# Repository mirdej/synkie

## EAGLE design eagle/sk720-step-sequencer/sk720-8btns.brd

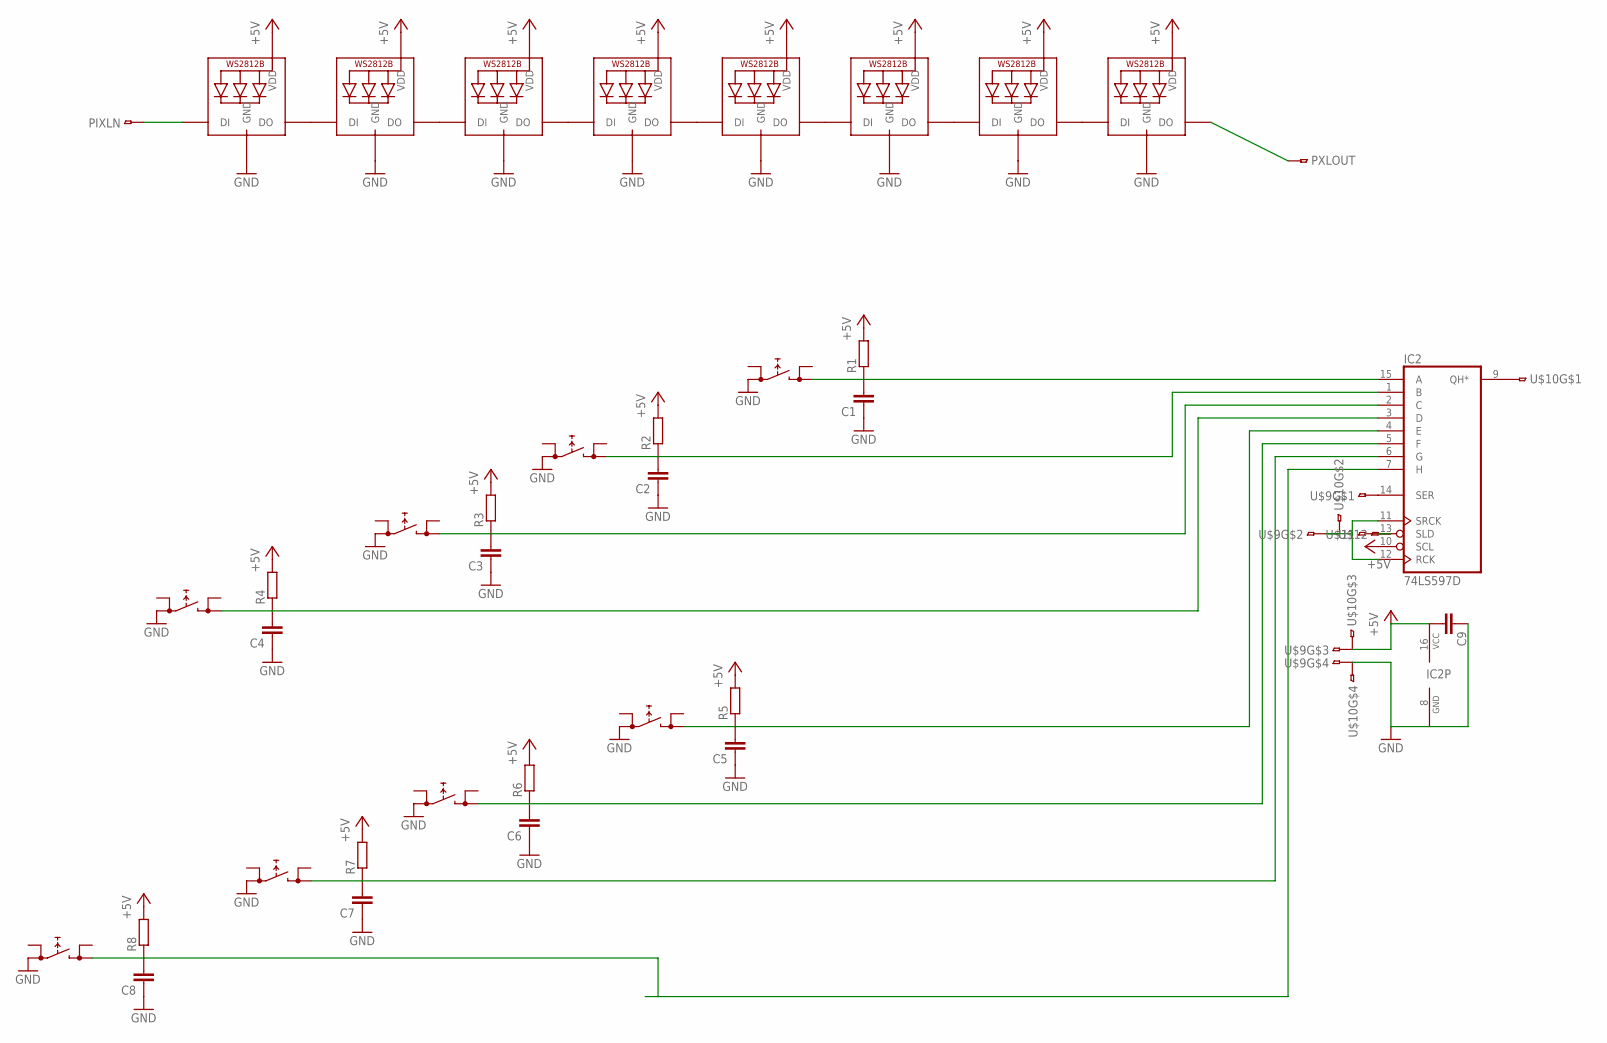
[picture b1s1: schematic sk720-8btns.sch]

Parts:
C1, C2, C3, C4, C5, C6, C7, C8: C-EUC0603; C0603
C9: C-EUC1206; C1206
IC2: 74LS597D; SO16
LED1, LED2, LED3, LED4, LED5, LED6, LED7, LED8: WS2812B5050; WS2812B
PIXLN: 1PINSMD
PXLOUT: 1PINSMD
R1, R2, R3, R4, R5, R6, R7, R8: R-EU_R1206; R1206
U$1, U$2, U$3, U$4, U$5, U$6, U$7, U$8: PRINTTASTER_SMDALPS-SKQ; SKQGAKE010
U$9, U$10: 4PIN-SMD; 4PIN-SMD-2.54
U$11, U$12: 1PINSMD

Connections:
+5V: C9.2, IC2.10 (SCL), IC2.16 (VCC), LED1.1-VDD (VDD), LED2.1-VDD (VDD), LED3.1-VDD (VDD), LED4.1-VDD (VDD), LED5.1-VDD (VDD), LED6.1-VDD (VDD), LED7.1-VDD (VDD), LED8.1-VDD (VDD), R1.2, R2.2, R3.2, R4.2, R5.2, R6.2, R7.2, R8.2, U$9.3, U$10.3
CLK: IC2.11 (SRCK), IC2.12 (RCK), U$9.2, U$10.2
GND: C1.1, C2.1, C3.1, C4.1, C5.1, C6.1, C7.1, C8.1, C9.1, IC2.8 (GND), LED1.3-GND (GND), LED2.3-GND (GND), LED3.3-GND (GND), LED4.3-GND (GND), LED5.3-GND (GND), LED6.3-GND (GND), LED7.3-GND (GND), LED8.3-GND (GND), U$1.2 (0), U$2.2 (0), U$3.2 (0), U$4.2 (0), U$5.2 (0), U$6.2 (0), U$7.2 (0), U$8.2 (0), U$9.4, U$10.4
LATCH: IC2.13 (SLD), U$11.2, U$12.2
MISO: IC2.9 (QH*), U$10.1
unnamed: C1.2, IC2.15 (A), R1.1, U$1.4 (1)
unnamed: C2.2, IC2.1 (B), R2.1, U$2.4 (1)
unnamed: C3.2, IC2.2 (C), R3.1, U$3.4 (1)
unnamed: C4.2, IC2.3 (D), R4.1, U$4.4 (1)
unnamed: C5.2, IC2.4 (E), R5.1, U$5.4 (1)
unnamed: C6.2, IC2.5 (F), R6.1, U$6.4 (1)
unnamed: C7.2, IC2.6 (G), R7.1, U$7.4 (1)
unnamed: IC2.14 (SER), U$9.1
unnamed: LED1.2-DOUT (DO), LED2.4-DIN (DI)
unnamed: C8.2, IC2.7 (H), R8.1, U$8.4 (1)
unnamed: LED2.2-DOUT (DO), LED3.4-DIN (DI)
unnamed: LED3.2-DOUT (DO), LED4.4-DIN (DI)
unnamed: LED4.2-DOUT (DO), LED5.4-DIN (DI)
unnamed: LED5.2-DOUT (DO), LED6.4-DIN (DI)
unnamed: LED6.2-DOUT (DO), LED7.4-DIN (DI)
unnamed: LED7.2-DOUT (DO), LED8.4-DIN (DI)
PXLIN: LED1.4-DIN (DI), PIXLN.2
PXLOUT: LED8.2-DOUT (DO), PXLOUT.2

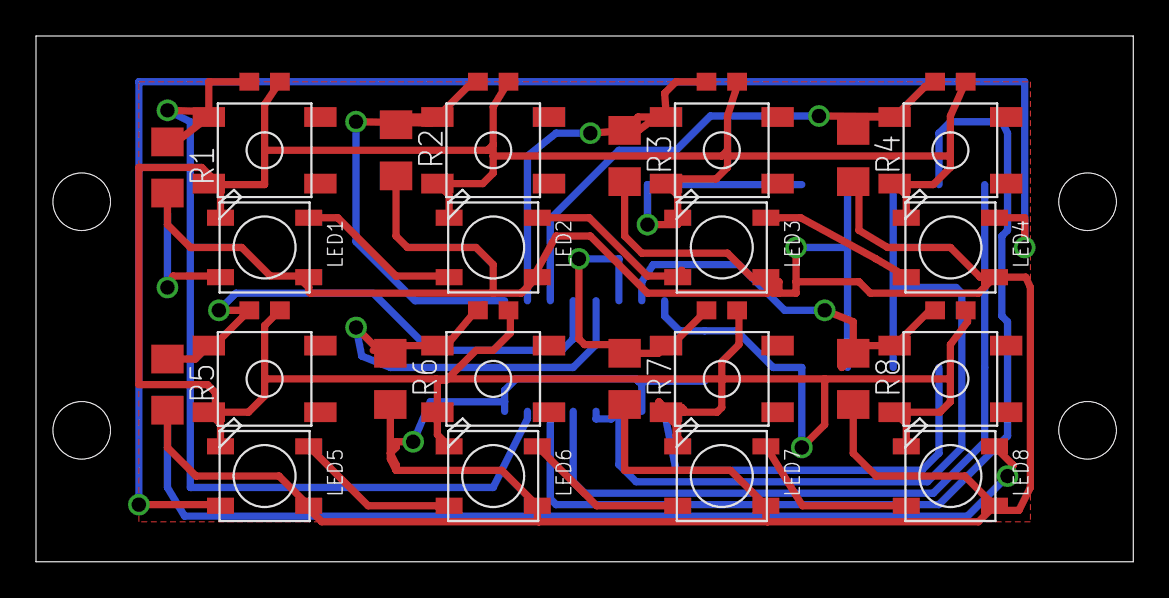
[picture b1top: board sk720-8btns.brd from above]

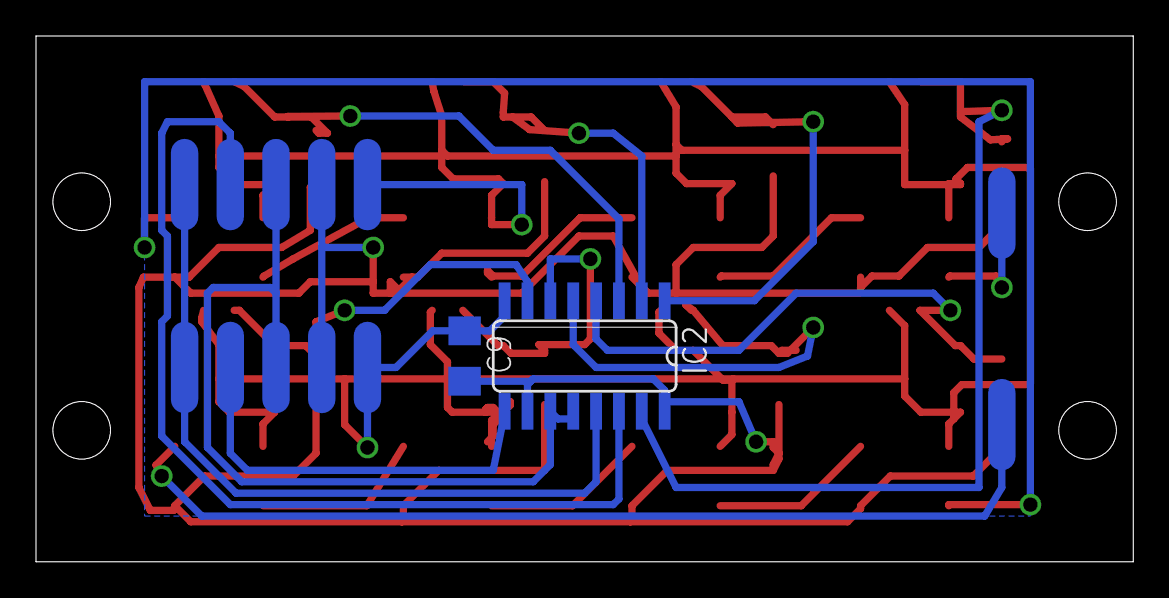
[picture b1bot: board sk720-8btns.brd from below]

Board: 2 copper layers, 61.0 x 29.2 mm, 40 parts (8 on the bottom side), 23 nets.

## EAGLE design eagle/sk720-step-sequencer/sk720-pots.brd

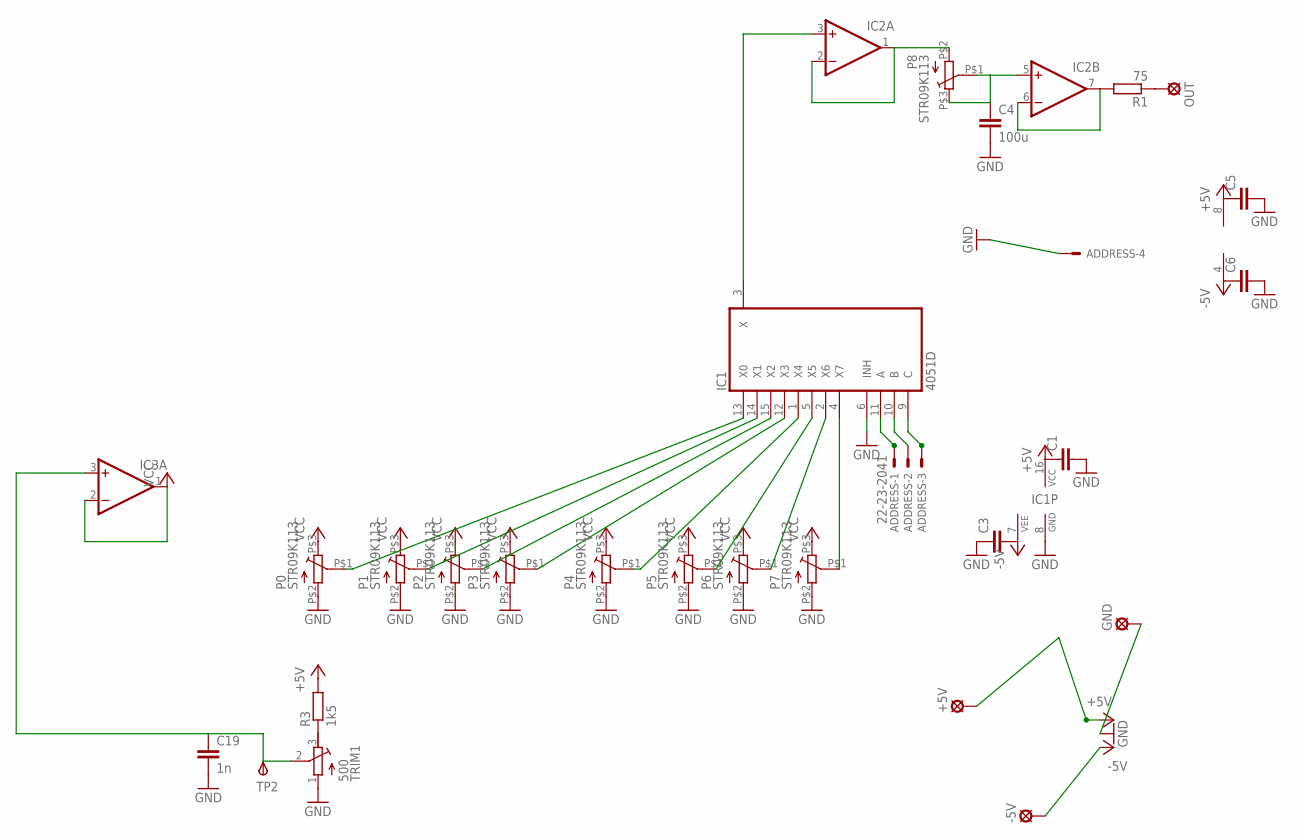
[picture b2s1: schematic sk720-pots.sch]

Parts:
+5V: LSP13
-5V: LSP13
ADDRESS: 22-23-2041
C1, C3, C5, C6: C-EUC0603; C0603
C4: 100u; C1608
C19: 1n; C1206
GND: LSP13
IC1: 4051D; SO16
IC2, IC3: DUAL_OPAMPD; SO08
OUT: LSP13
P0, P1, P2, P3, P4, P5, P6, P7, P8: STR09K113
R1: 75; R1206
R3: 1k5; R1206
TP2: TPSPAD1-13; P1-13
TRIM1: 500; RTRIM64Y

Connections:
+5V: +5V.MP, C1.1, C5.1, IC1.16 (VCC), IC2.8 (V+), R3.2
-5V: -5V.MP, C3.2, C6.1, IC1.7 (VEE), IC2.4 (V-)
GND: ADDRESS.4, C1.2, C3.1, C4.2, C5.2, C6.2, C19.2, GND.MP, IC1.6 (INH), IC1.8 (GND), P0.P$2 (ANFANG), P1.P$2 (ANFANG), P2.P$2 (ANFANG), P3.P$2 (ANFANG), P4.P$2 (ANFANG), P5.P$2 (ANFANG), P6.P$2 (ANFANG), P7.P$2 (ANFANG), TRIM1.1 (E)
unnamed: IC1.1 (X4), P4.P$1 (SCHLEIFER)
unnamed: IC1.5 (X5), P5.P$1 (SCHLEIFER)
unnamed: IC1.2 (X6), P6.P$1 (SCHLEIFER)
unnamed: IC1.4 (X7), P7.P$1 (SCHLEIFER)
unnamed: OUT.MP, R1.1
unnamed: ADDRESS.1, IC1.11 (A)
unnamed: R3.1, TRIM1.3 (A)
unnamed: IC2.6 (-IN), IC2.7 (OUT), R1.2
unnamed: IC1.3 (X), IC2.3 (+IN)
unnamed: IC2.1 (OUT), IC2.2 (-IN), P8.P$2 (ANFANG)
unnamed: C4.1, IC2.5 (+IN), P8.P$1 (SCHLEIFER), P8.P$3 (ENDE)
unnamed: ADDRESS.2, IC1.10 (B)
unnamed: C19.1, IC3.3 (+IN), TP2.TP, TRIM1.2 (S)
unnamed: IC1.13 (X0), P0.P$1 (SCHLEIFER)
unnamed: IC1.14 (X1), P1.P$1 (SCHLEIFER)
unnamed: IC1.15 (X2), P2.P$1 (SCHLEIFER)
unnamed: IC1.12 (X3), P3.P$1 (SCHLEIFER)
unnamed: ADDRESS.3, IC1.9 (C)
V+: IC3.8 (V+)
V-: IC3.4 (V-)
VCC: IC3.1 (OUT), IC3.2 (-IN), P0.P$3 (ENDE), P1.P$3 (ENDE), P2.P$3 (ENDE), P3.P$3 (ENDE), P4.P$3 (ENDE), P5.P$3 (ENDE), P6.P$3 (ENDE), P7.P$3 (ENDE)

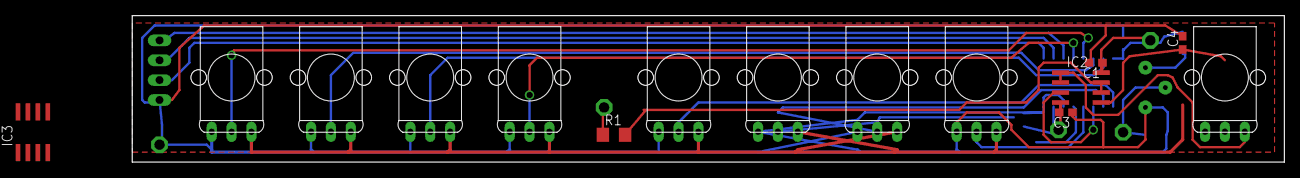
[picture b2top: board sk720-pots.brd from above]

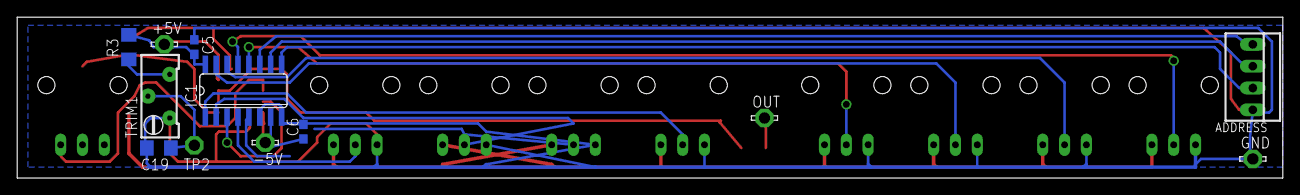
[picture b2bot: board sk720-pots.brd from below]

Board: 2 copper layers, 147.3 x 18.7 mm, 27 parts (12 on the bottom side), 22 nets.

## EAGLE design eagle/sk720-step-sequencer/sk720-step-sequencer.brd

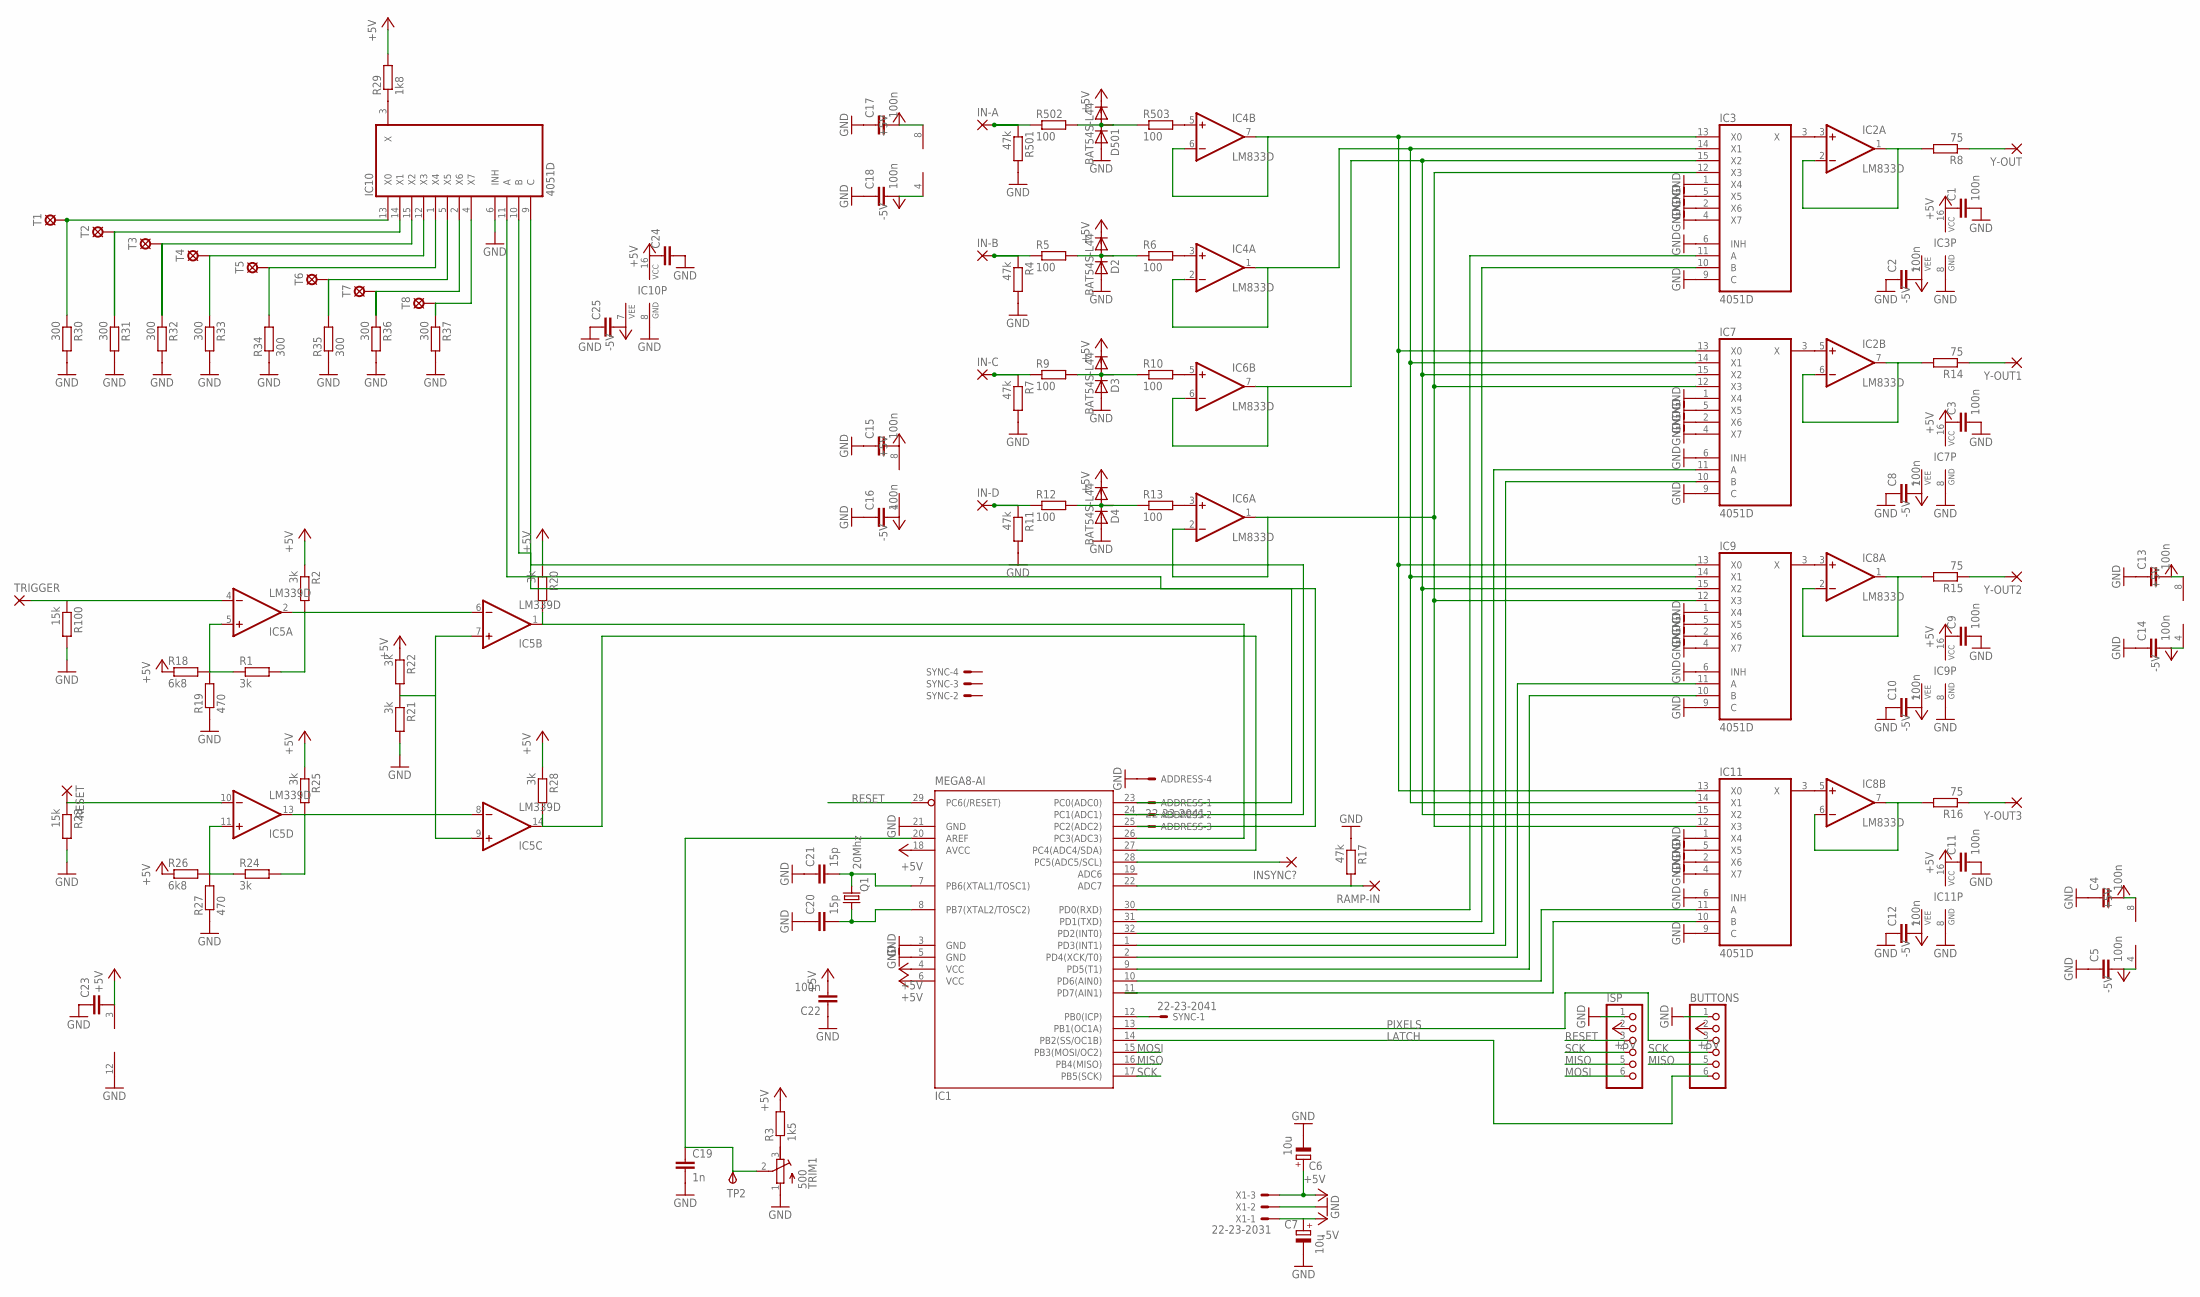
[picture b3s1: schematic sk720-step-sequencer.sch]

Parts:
ADDRESS: 22-23-2041
BUTTONS: PINHD-1X6; 1X06
C1, C2, C3, C4, C5, C8, C9, C10, C11, C12, C13, C14, C15, C16, C17, C18, C22: 100n; C0603
C6, C7: 10u; CT3528
C19: 1n; C1206
C20, C21: 15p; C1206
C23: C-EUC1206; C1206
C24, C25: C-EUC0603; C0603
D2, D3, D4, D501: BAT54S-L44; SOT23
IC1: MEGA8-AI; TQFP32-08
IC2, IC4, IC6, IC8: LM833D; SO08
IC3, IC7, IC9, IC10, IC11: 4051D; SO16
IC5: LM339D; SO14
IN-A: 3,17/1,1
IN-B: 3,17/1,1
IN-C: 3,17/1,1
IN-D: 3,17/1,1
INSYNC?: 3,17/1,1
ISP: PINHD-1X6; 1X06
Q1: 20Mhz; HC49UP
R1, R2, R20, R21, R22, R24, R25, R28: 3k; R1206
R3: 1k5; R1206
R4, R7, R11, R17, R501: 47k; R1206
R5, R6, R9, R10, R12, R13, R502, R503: 100; R1206
R8, R14, R15, R16: 75; R1206
R18, R26: 6k8; R1206
R19, R27: 470; R1206
R23, R100: 15k; R1206
R29: 1k8; R1206
R30, R31, R32, R33, R34, R35, R36, R37: 300; R1206
RAMP-IN: 3,17/1,1
RESET: 3,17/1,1
SYNC: 22-23-2041
T1, T2, T3, T4, T5, T6, T7, T8: LSP13
TP2: TPSPAD1-13; P1-13
TRIGGER: 3,17/1,1
TRIM1: 500; RTRIM64Y
X1: 22-23-2031
Y-OUT, Y-OUT1, Y-OUT2, Y-OUT3: 3,17/1,1

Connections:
+5V: BUTTONS.2, C1.1, C3.1, C4.2, C6.+, C9.1, C11.1, C13.2, C15.2, C17.2, C22.2, C23.2, C24.1, D2.2 (C), D3.2 (C), D4.2 (C), D501.2 (C), IC1.4 (VCC), IC1.6 (VCC), IC1.18 (AVCC), IC2.8 (V+), IC3.16 (VCC), IC4.8 (V+), IC5.3 (V+), IC6.8 (V+), IC7.16 (VCC), IC8.8 (V+), IC9.16 (VCC), IC10.16 (VCC), IC11.16 (VCC), ISP.2, R2.1, R3.2, R18.1, R20.1, R22.1, R25.1, R26.1, R28.1, R29.2, X1.3
-5V: C2.2, C5.2, C7.+, C8.2, C10.2, C12.2, C14.2, C16.2, C18.2, C25.2, IC2.4 (V-), IC3.7 (VEE), IC4.4 (V-), IC6.4 (V-), IC7.7 (VEE), IC8.4 (V-), IC9.7 (VEE), IC10.7 (VEE), IC11.7 (VEE), X1.1
GND: ADDRESS.4, BUTTONS.1, C1.2, C2.1, C3.2, C4.1, C5.1, C6.-, C7.-, C8.1, C9.2, C10.1, C11.2, C12.1, C13.1, C14.1, C15.1, C16.1, C17.1, C18.1, C19.2, C20.1, C21.1, C22.1, C23.1, C24.2, C25.1, D2.1 (A), D3.1 (A), D4.1 (A), D501.1 (A), IC1.3 (GND), IC1.5 (GND), IC1.21 (GND), IC3.1 (X4), IC3.2 (X6), IC3.4 (X7), IC3.5 (X5), IC3.6 (INH), IC3.8 (GND), IC3.9 (C), IC5.12 (GND), IC7.1 (X4), IC7.2 (X6), IC7.4 (X7), IC7.5 (X5), IC7.6 (INH), IC7.8 (GND), IC7.9 (C), IC9.1 (X4), IC9.2 (X6), IC9.4 (X7), IC9.5 (X5), IC9.6 (INH), IC9.8 (GND), IC9.9 (C), IC10.6 (INH), IC10.8 (GND), IC11.1 (X4), IC11.2 (X6), IC11.4 (X7), IC11.5 (X5), IC11.6 (INH), IC11.8 (GND), IC11.9 (C), ISP.1, R4.2, R7.2, R11.2, R17.1, R19.1, R21.2, R23.2, R27.1, R30.2, R31.2, R32.2, R33.2, R34.1, R35.1, R36.2, R37.2, R100.2, R501.2, TRIM1.1 (E), X1.2
IN: IC3.12 (X3), IC6.1 (OUT), IC6.2 (-IN), IC7.12 (X3), IC9.12 (X3), IC11.12 (X3)
IN1: IC3.13 (X0), IC4.6 (-IN), IC4.7 (OUT), IC7.13 (X0), IC9.13 (X0), IC11.13 (X0)
IN2: IC3.14 (X1), IC4.1 (OUT), IC4.2 (-IN), IC7.14 (X1), IC9.14 (X1), IC11.14 (X1)
IN3: IC3.15 (X2), IC6.6 (-IN), IC6.7 (OUT), IC7.15 (X2), IC9.15 (X2), IC11.15 (X2)
LATCH: BUTTONS.6, IC1.14 (PB2(SS/OC1B))
MISO: BUTTONS.5, IC1.16 (PB4(MISO)), ISP.5
MOSI: IC1.15 (PB3(MOSI/OC2)), ISP.6
unnamed: IC2.3 (+IN), IC3.3 (X)
unnamed: IC4.5 (+IN), R503.2
unnamed: IC1.28 (PC5(ADC5/SCL)), INSYNC?.1
unnamed: IC1.12 (PB0(ICP)), SYNC.1
unnamed: R3.1, TRIM1.3 (A)
unnamed: ADDRESS.1, IC1.23 (PC0(ADC0)), IC10.11 (A)
unnamed: IN-B.1, R4.1, R5.1
unnamed: D2.3 (AC), R5.2, R6.1
unnamed: IC4.3 (+IN), R6.2
unnamed: IN-A.1, R501.1, R502.1
unnamed: D501.3 (AC), R502.2, R503.1
unnamed: R8.1, Y-OUT.1
unnamed: IC5.4 (-IN), R100.1, TRIGGER.1
unnamed: IC2.1 (OUT), IC2.2 (-IN), R8.2
unnamed: IN-C.1, R7.1, R9.1
unnamed: D3.3 (AC), R9.2, R10.1
unnamed: IC6.5 (+IN), R10.2
unnamed: IC1.30 (PD0(RXD)), IC3.11 (A)
unnamed: IN-D.1, R11.1, R12.1
unnamed: D4.3 (AC), R12.2, R13.1
unnamed: IC6.3 (+IN), R13.2
unnamed: IC5.2 (OUT), IC5.6 (-IN), R1.2, R2.2
unnamed: IC2.6 (-IN), IC2.7 (OUT), R14.2
unnamed: R14.1, Y-OUT1.1
unnamed: IC2.5 (+IN), IC7.3 (X)
unnamed: IC8.1 (OUT), IC8.2 (-IN), R15.2
unnamed: R15.1, Y-OUT2.1
unnamed: IC8.3 (+IN), IC9.3 (X)
unnamed: IC8.6 (-IN), IC8.7 (OUT), R16.2
unnamed: R16.1, Y-OUT3.1
unnamed: IC8.5 (+IN), IC11.3 (X)
unnamed: IC5.5 (+IN), R1.1, R18.2, R19.2
unnamed: IC1.31 (PD1(TXD)), IC3.10 (B)
unnamed: IC1.32 (PD2(INT0)), IC7.11 (A)
unnamed: IC1.1 (PD3(INT1)), IC7.10 (B)
unnamed: IC1.2 (PD4(XCK/T0)), IC9.11 (A)
unnamed: IC1.9 (PD5(T1)), IC9.10 (B)
unnamed: IC1.10 (PD6(AIN0)), IC11.11 (A)
unnamed: IC1.11 (PD7(AIN1)), IC11.10 (B)
unnamed: IC1.22 (ADC7), R17.2, RAMP-IN.1
unnamed: ADDRESS.2, IC1.24 (PC1(ADC1)), IC10.10 (B)
unnamed: ADDRESS.3, IC1.25 (PC2(ADC2)), IC10.9 (C)
unnamed: C21.2, IC1.7 (PB6(XTAL1/TOSC1)), Q1.2
unnamed: C20.2, IC1.8 (PB7(XTAL2/TOSC2)), Q1.1
unnamed: IC1.26 (PC3(ADC3)), IC5.1 (OUT), R20.2
unnamed: IC5.7 (+IN), IC5.9 (+IN), R21.1, R22.2
unnamed: IC5.10 (-IN), R23.1, RESET.1
unnamed: IC5.8 (-IN), IC5.13 (OUT), R24.2, R25.2
unnamed: IC5.11 (+IN), R24.1, R26.2, R27.2
unnamed: IC1.27 (PC4(ADC4/SDA)), IC5.14 (OUT), R28.2
unnamed: IC10.13 (X0), R30.1, T1.MP
unnamed: IC10.14 (X1), R31.1, T2.MP
unnamed: IC10.15 (X2), R32.1, T3.MP
unnamed: IC10.12 (X3), R33.1, T4.MP
unnamed: IC10.1 (X4), R34.2, T5.MP
unnamed: IC10.5 (X5), R35.2, T6.MP
unnamed: IC10.2 (X6), R36.1, T7.MP
unnamed: IC10.4 (X7), R37.1, T8.MP
unnamed: C19.1, IC1.20 (AREF), TP2.TP, TRIM1.2 (S)
unnamed: IC10.3 (X), R29.1
PIXELS: BUTTONS.3, IC1.13 (PB1(OC1A))
RESET: IC1.29 (PC6(/RESET)), ISP.3
SCK: BUTTONS.4, IC1.17 (PB5(SCK)), ISP.4

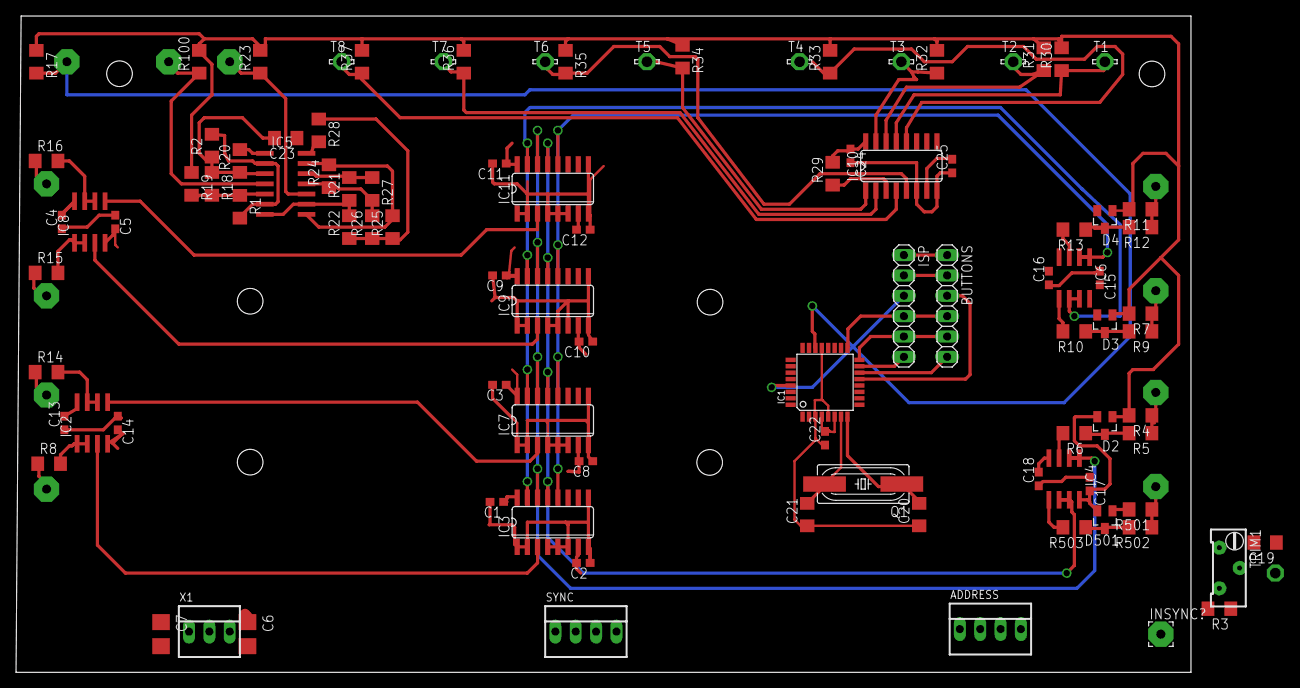
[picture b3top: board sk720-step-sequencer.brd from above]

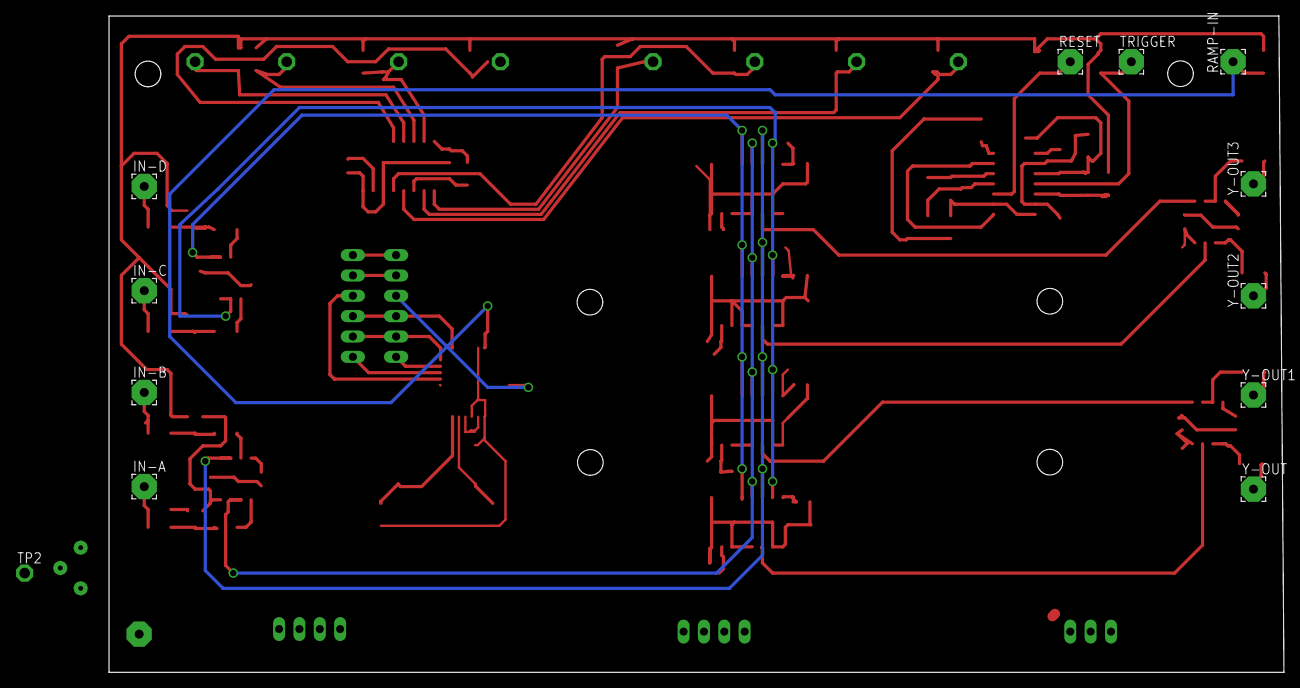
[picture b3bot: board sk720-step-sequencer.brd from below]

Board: 2 copper layers, 146.6 x 81.9 mm, 109 parts (12 on the bottom side), 73 nets.

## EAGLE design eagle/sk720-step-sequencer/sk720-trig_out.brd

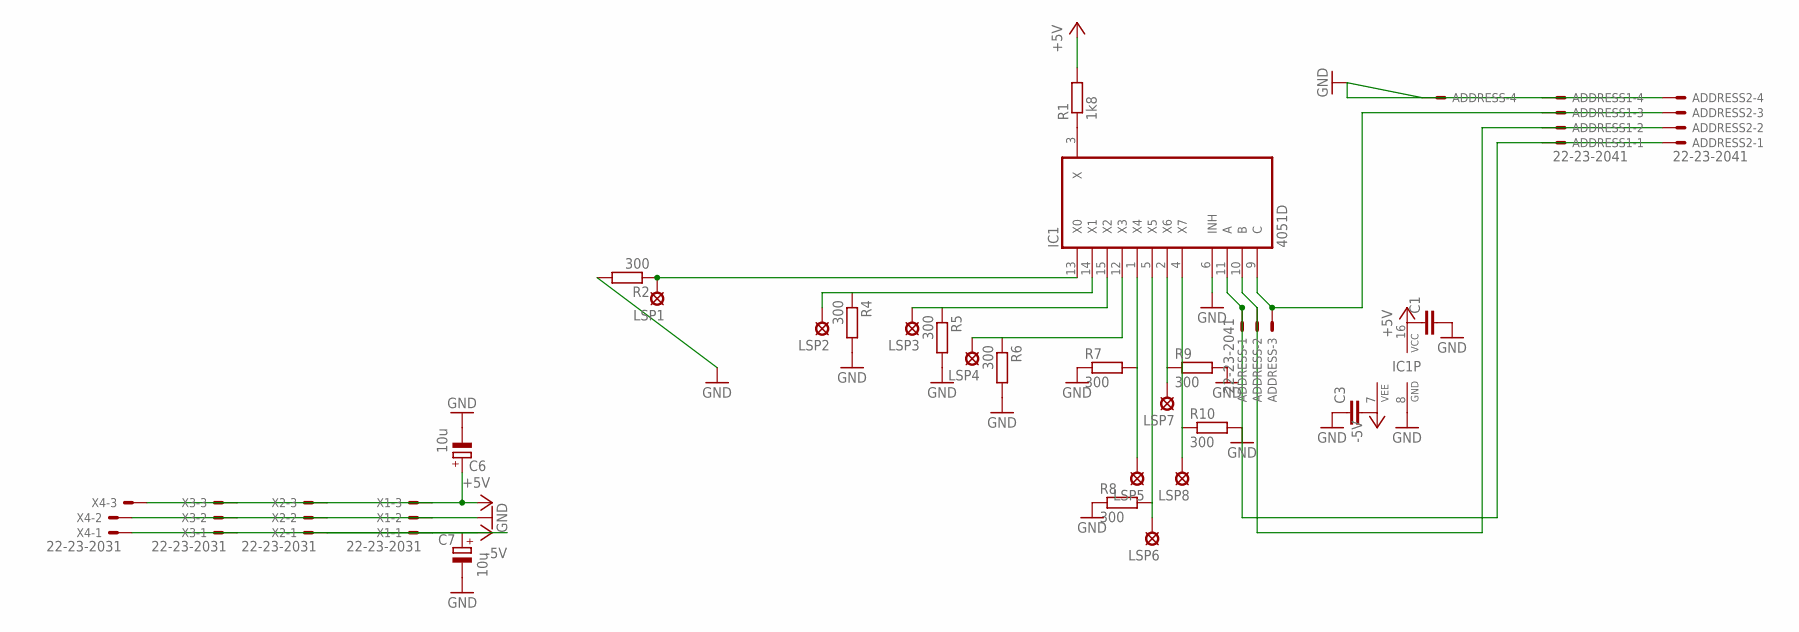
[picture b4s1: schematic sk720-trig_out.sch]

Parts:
ADDRESS, ADDRESS1, ADDRESS2: 22-23-2041
C1, C3: C-EUC0603; C0603
C6, C7: 10u; CT3528
IC1: 4051D; SO16
LSP1, LSP2, LSP3, LSP4, LSP5, LSP6, LSP7, LSP8: LSP13
R1: 1k8; R1206
R2, R4, R5, R6, R7, R8, R9, R10: 300; R1206
X1, X2, X3, X4: 22-23-2031

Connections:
+5V: C1.1, C6.+, IC1.16 (VCC), R1.2, X1.3, X2.3, X3.3, X4.3
-5V: C3.2, C7.+, IC1.7 (VEE), X1.1, X2.1, X3.1, X4.1
GND: ADDRESS.4, ADDRESS1.4, ADDRESS2.4, C1.2, C3.1, C6.-, C7.-, IC1.6 (INH), IC1.8 (GND), R2.2, R4.2, R5.2, R6.2, R7.1, R8.1, R9.2, R10.2, X1.2, X2.2, X3.2, X4.2
unnamed: IC1.1 (X4), LSP5.MP, R7.2
unnamed: IC1.5 (X5), LSP6.MP, R8.2
unnamed: IC1.2 (X6), LSP7.MP, R9.1
unnamed: IC1.4 (X7), LSP8.MP, R10.1
unnamed: IC1.3 (X), R1.1
unnamed: ADDRESS.1, ADDRESS1.1, ADDRESS2.1, IC1.11 (A)
unnamed: ADDRESS.2, ADDRESS1.2, ADDRESS2.2, IC1.10 (B)
unnamed: IC1.13 (X0), LSP1.MP, R2.1
unnamed: IC1.14 (X1), LSP2.MP, R4.1
unnamed: IC1.15 (X2), LSP3.MP, R5.1
unnamed: IC1.12 (X3), LSP4.MP, R6.1
unnamed: ADDRESS.3, ADDRESS1.3, ADDRESS2.3, IC1.9 (C)

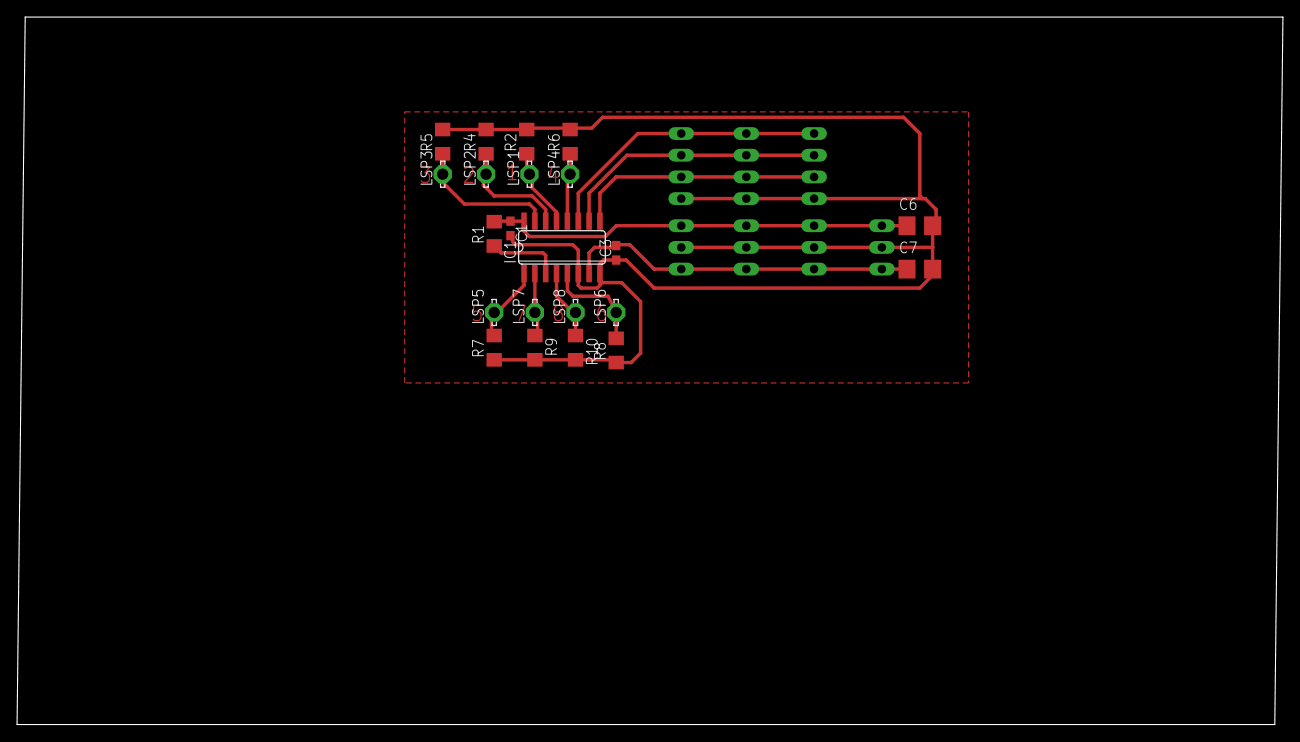
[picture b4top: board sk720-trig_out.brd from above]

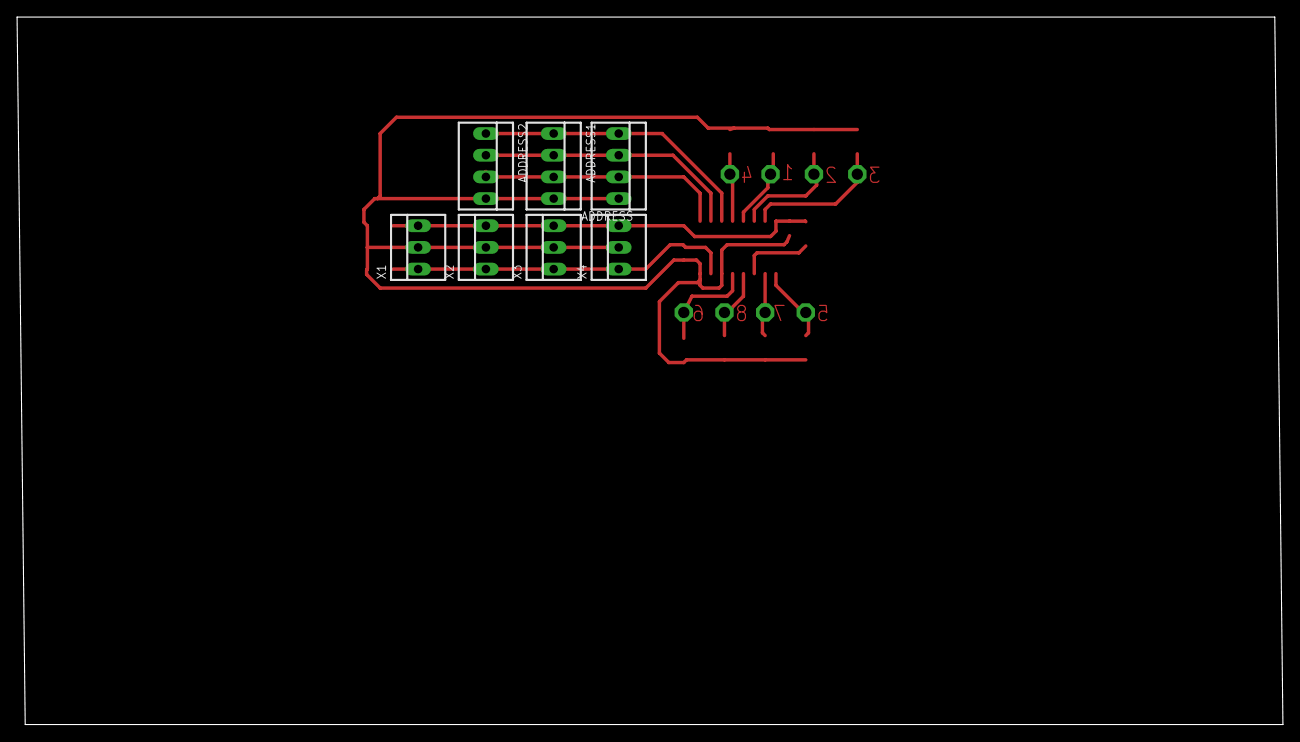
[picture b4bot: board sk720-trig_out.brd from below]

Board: 2 copper layers, 148.3 x 82.9 mm, 29 parts (7 on the bottom side), 15 nets.

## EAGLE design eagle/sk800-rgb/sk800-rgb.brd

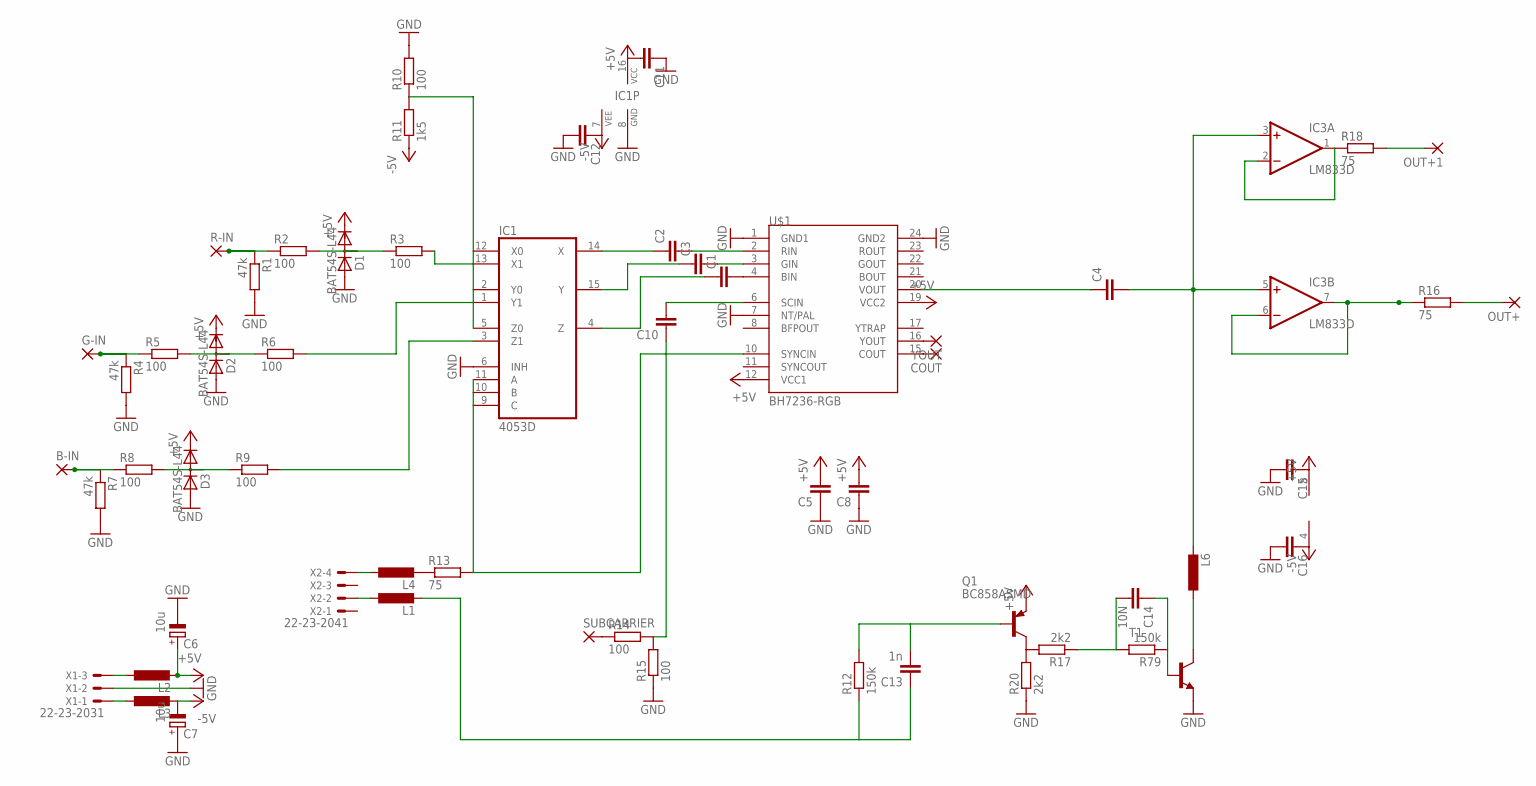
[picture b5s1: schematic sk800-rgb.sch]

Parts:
B-IN: 3,17/1,1
C1, C2, C3, C4, C10: C-EUC1206; C1206
C5, C8, C11, C12, C15, C16: C-EUC0603; C0603
C6, C7: 10u; CT3528
C13: 1n; C1206
C14: 10N; C1206
COUT: 3,17/1,1
D1, D2, D3: BAT54S-L44; SOT23
G-IN: 3,17/1,1
IC1: 4053D; SO16
IC3: LM833D; SO08
L1, L2, L3, L4, L6: L-EUL5038P; L5038P
OUT+, OUT+1: 3,17/1,1
Q1: BC858ASMD; SOT23-BEC
R1, R4, R7: 47k; R1206
R2, R3, R5, R6, R8, R9, R10, R14, R15: 100; R1206
R11: 1k5; R1206
R12, R79: 150k; R1206
R13, R16, R18: 75; R1206
R17, R20: 2k2; R1206
R-IN: 3,17/1,1
SUBCARRIER: 3,17/1,1
T1: BC847ALT1-NPN-SOT23-BEC; SOT23-BEC
U$1: BH7236-RGB; SO24N
X1: 22-23-2031
X2: 22-23-2041
YOUT: 3,17/1,1

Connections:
+5V: C5.2, C6.+, C8.2, C11.2, C15.1, D1.2 (C), D2.2 (C), D3.2 (C), IC1.16 (VCC), IC3.8 (V+), L2.2, Q1.E, U$1.12 (VCC1), U$1.19 (VCC2)
-5V: C7.-, C12.1, C16.1, IC1.7 (VEE), IC3.4 (V-), L3.2, R11.1
GND: C5.1, C6.-, C7.+, C8.1, C11.1, C12.2, C15.2, C16.2, D1.1 (A), D2.1 (A), D3.1 (A), IC1.6 (INH), IC1.8 (GND), R1.2, R4.2, R7.2, R10.2, R15.1, R20.1, T1.E, U$1.1 (GND1), U$1.7 (NT/PAL), U$1.24 (GND2), X1.2
unnamed: C1.2, U$1.4 (BIN)
unnamed: C2.1, IC1.14 (X)
unnamed: C2.2, U$1.2 (RIN)
unnamed: C3.2, U$1.3 (GIN)
unnamed: R1.1, R2.1, R-IN.1
unnamed: D1.3 (AC), R2.2, R3.1
unnamed: IC1.13 (X1), R3.2
unnamed: C3.1, IC1.15 (Y)
unnamed: C1.1, IC1.4 (Z)
unnamed: C10.2, U$1.6 (SCIN)
unnamed: L2.1, X1.3
unnamed: L1.1, X2.2
unnamed: L4.1, X2.4
unnamed: G-IN.1, R4.1, R5.1
unnamed: L3.1, X1.1
unnamed: D2.3 (AC), R5.2, R6.1
unnamed: IC1.1 (Y1), R6.2
unnamed: B-IN.1, R7.1, R8.1
unnamed: D3.3 (AC), R8.2, R9.1
unnamed: IC1.3 (Z1), R9.2
unnamed: IC1.9 (C), IC1.10 (B), IC1.11 (A), R13.2, U$1.10 (SYNCIN)
unnamed: IC1.2 (Y0), IC1.5 (Z0), IC1.12 (X0), R10.1, R11.2
unnamed: C4.1, U$1.20 (VOUT)
unnamed: C13.1, L1.2, R12.1
unnamed: U$1.16 (YOUT), YOUT.1
unnamed: L4.2, R13.1
unnamed: COUT.1, U$1.15 (COUT)
unnamed: R14.1, SUBCARRIER.1
unnamed: C10.1, R14.2, R15.2
unnamed: OUT+.1, R16.2
unnamed: IC3.6 (-IN), IC3.7 (OUT), R16.1
unnamed: C4.2, IC3.3 (+IN), IC3.5 (+IN), L6.2
unnamed: L6.1, T1.C
unnamed: C14.1, R79.1, T1.B
unnamed: C13.2, Q1.B, R12.2
unnamed: Q1.C, R17.2, R20.2
unnamed: C14.2, R17.1, R79.2
unnamed: OUT+1.1, R18.2
unnamed: IC3.1 (OUT), IC3.2 (-IN), R18.1
